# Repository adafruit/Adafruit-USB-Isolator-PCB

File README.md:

# Adafruit USB Isolator PCB
<a href="http://www.adafruit.com/products/2107"><br/>
Click here to purchase one from the Adafruit shop</a>

This handy little low-cost USB Isolator is exactly what you need to provide protection against harmful noise, ground loops, surges, and spikes. Works with any 1.5Mbps (low speed) or 12Mbps (full speed) USB device. Not for high speed USB devices, often used for video cameras (check your product to make sure its low/full compatible) Based on Analog Device's USB isolators

PCB files for the Adafruit USB Isolator. The format is EagleCAD schematic and board layout
- https://www.adafruit.com/product/2107

### License

Adafruit invests time and resources providing this open source design, please support Adafruit and open-source hardware by purchasing products from [Adafruit](https://www.adafruit.com)!

All text above must be included in any redistribution

Designed by Limor Fried/Ladyada for Adafruit Industries.
Creative Commons Attribution/Share-Alike, all text above must be included in any redistribution. 
See license.txt for additional information.

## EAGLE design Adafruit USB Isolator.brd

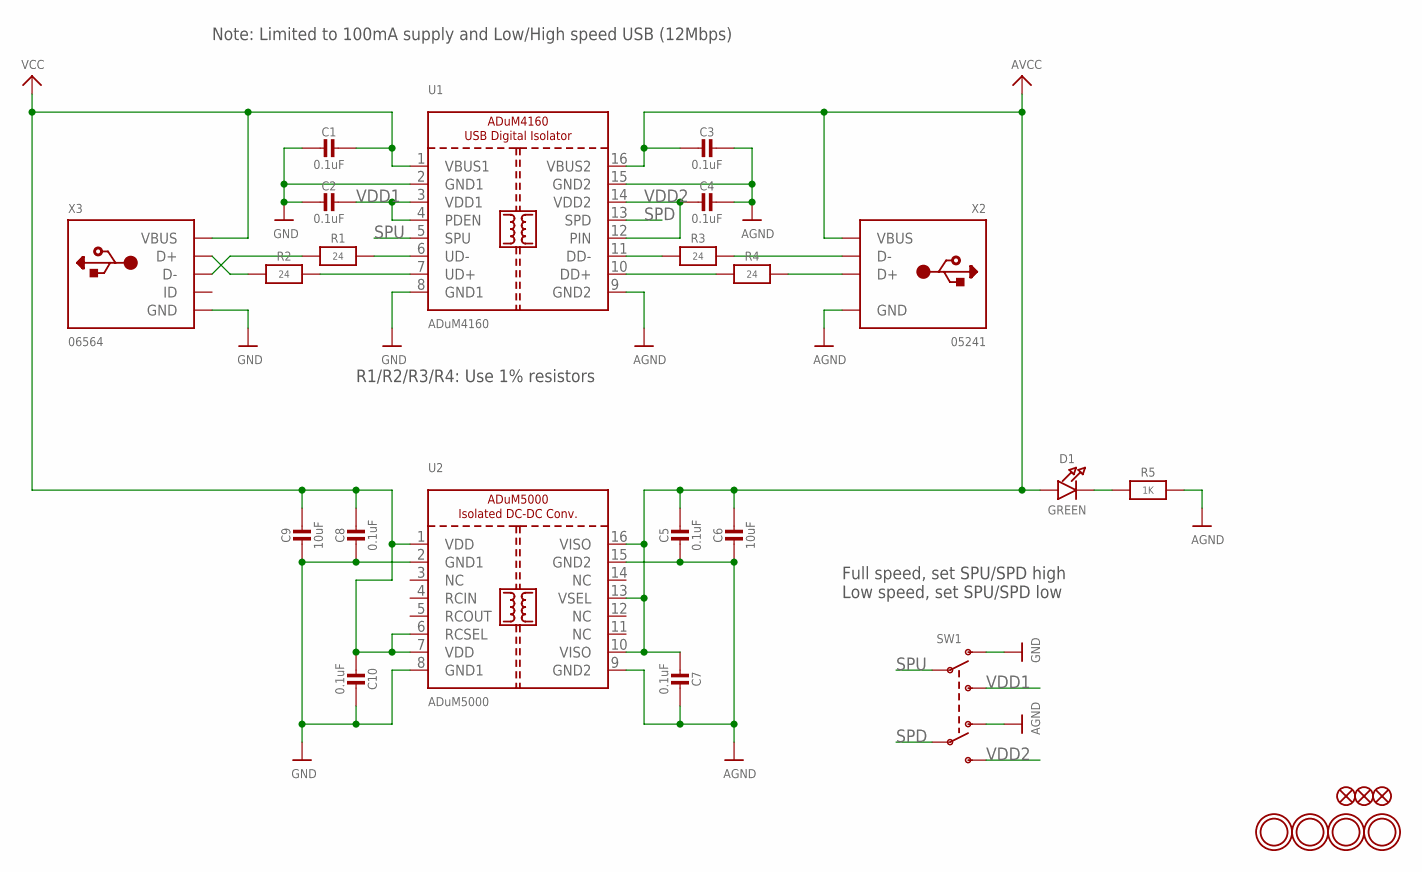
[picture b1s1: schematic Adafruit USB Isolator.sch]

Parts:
C1, C2, C3, C4, C5, C7, C8, C10: 0.1uF; 0805-NO
C6, C9: 10uF; 0805-NO
D1: GREEN; CHIPLED_0805_NOOUTLINE
FID1, FID2, FID3: FIDUCIAL""; FIDUCIAL_1MM
R1, R2, R3: 24; 0805-NO
R4: 24; _0805MP
R5: 1K; 0805-NO
SW1: SWITCH_DPDTEG1390; EG1390
U1: ADuM4160; SOIC16WIDE
U2: ADuM5000; SOIC16WIDE
U$7, U$8, U$9, U$10: MOUNTINGHOLE2.5_THICK; MOUNTINGHOLE_2.5_PLATED_THICK
X2: 05241; USB_HOST-PTH
X3: 06564; USB-MINIB_LARGER

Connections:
AGND: C3.1, C4.1, C5.2, C6.2, C7.1, R5.2, SW1.O2, U1.9 (GND2), U1.15 (GND2), U2.9 (GND2), U2.15 (GND2), X2.GND
AVCC: C3.2, C5.1, C6.1, C7.2, D1.A, U1.16 (VBUS2), U2.10 (VISO), U2.13 (VSEL), U2.16 (VISO), X2.VBUS
GND: C1.2, C2.2, C8.2, C9.2, C10.1, SW1.O1, U1.2 (GND1), U1.8 (GND1), U2.2 (GND1), U2.8 (GND1), X3.GND, X3.GND1 (GND), X3.GND2 (GND), X3.GND3 (GND), X3.GND4 (GND)
unnamed: R2.1, X3.D+
unnamed: R2.2, U1.7 (UD+)
unnamed: R1.2, U1.6 (UD-)
unnamed: R1.1, X3.D-
unnamed: R4.1, U1.10 (DD+)
unnamed: R4.2, X2.D+
unnamed: R3.2, X2.D-
unnamed: R3.1, U1.11 (DD-)
unnamed: D1.C, R5.1
SPD: SW1.P2, U1.13 (SPD)
SPU: SW1.P1, U1.5 (SPU)
VCC: C1.1, C8.1, C9.1, C10.2, U1.1 (VBUS1), U2.1 (VDD), U2.6 (RCSEL), U2.7 (VDD), X3.VBUS
VDD1: C2.1, SW1.S1, U1.3 (VDD1), U1.4 (PDEN)
VDD2: C4.2, SW1.S2, U1.12 (PIN), U1.14 (VDD2)

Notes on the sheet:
R1/R2/R3/R4: Use 1% resistors
Note: Limited to 100mA supply and Low/High speed USB (12Mbps)
Full speed, set SPU/SPD high Low speed, set SPU/SPD low

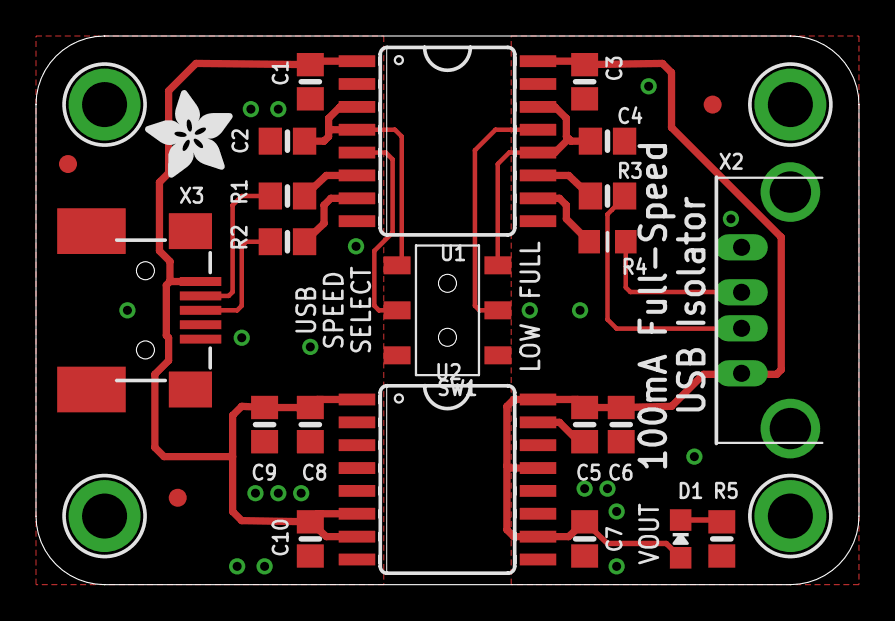
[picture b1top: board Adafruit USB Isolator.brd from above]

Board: 2 copper layers, 45.7 x 30.5 mm, 30 parts (1 on the bottom side), 17 nets.

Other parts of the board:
U$14: ADAFRUIT_5MM
U$16: ADAFRUIT_TEXT_30MM

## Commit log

2015-04-26 init

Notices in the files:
parts and their libraries:
microbuilder: This work is placed in the public domain, and may be freely used for commercial and non-commercial work with the following conditions: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
